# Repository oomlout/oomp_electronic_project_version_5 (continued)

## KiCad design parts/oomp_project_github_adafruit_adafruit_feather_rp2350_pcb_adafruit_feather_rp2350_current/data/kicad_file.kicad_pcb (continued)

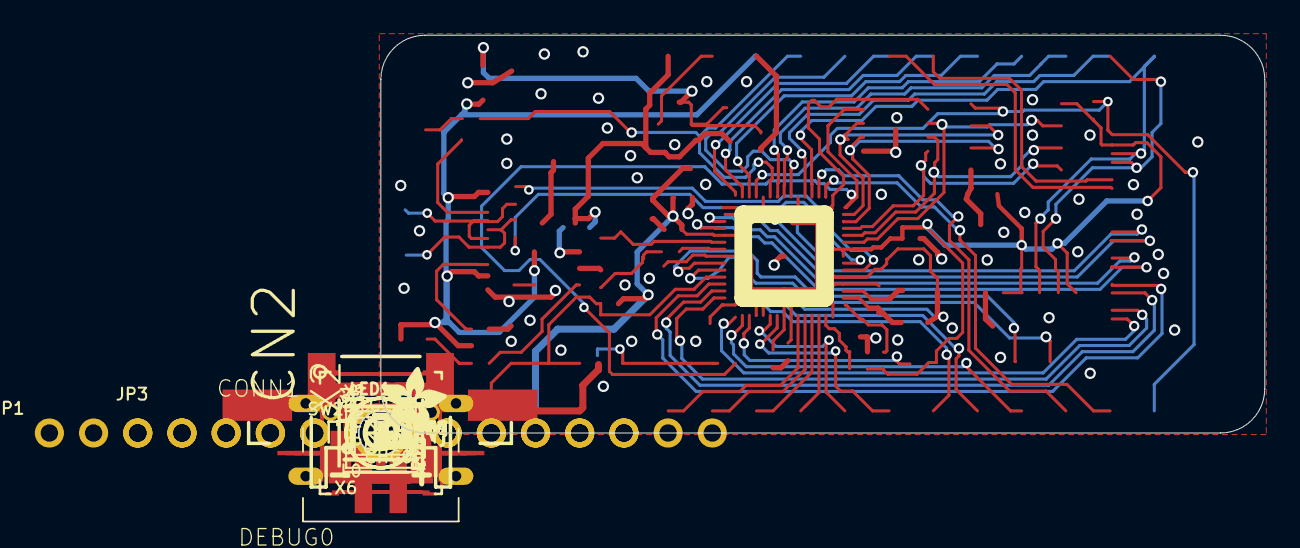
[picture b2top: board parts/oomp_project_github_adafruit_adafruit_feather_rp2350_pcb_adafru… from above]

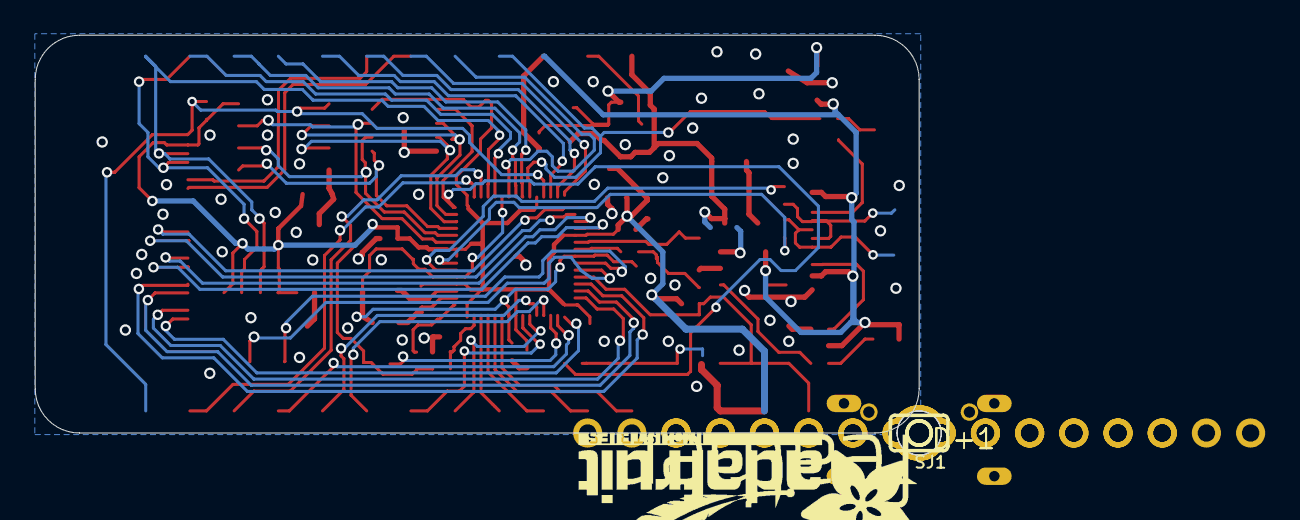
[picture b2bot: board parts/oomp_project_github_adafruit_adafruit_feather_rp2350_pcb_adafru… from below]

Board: 2 copper layers, 50.8 x 22.9 mm, 145 parts (39 on the bottom side), 64 nets.

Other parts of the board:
PLABEL0: PLABEL0
PLABEL1: PLABEL1
PLABEL2: PLABEL2
PLABEL3: PLABEL3
PLABEL4: PLABEL4
PLABEL5: PLABEL5
PLABEL6: PLABEL6
PLABEL7: PLABEL7
PLABEL8: PLABEL8
PLABEL9: PLABEL9
PLABEL10: PLABEL10
PLABEL11: PLABEL11
PLABEL12: PLABEL12
PLABEL13: PLABEL13
PLABEL14: PLABEL14
PLABEL15: PLABEL15
PLABEL16: PLABEL16
PLABEL17: PLABEL17
PLABEL18: PLABEL18
PLABEL19: PLABEL19
PLABEL20: PLABEL20
PLABEL21: PLABEL21
PLABEL22: PLABEL22
PLABEL23: PLABEL23
PLABEL24: PLABEL24
PLABEL25: PLABEL25
PLABEL26: PLABEL26
PLABEL27: PLABEL27
PLABEL28: PLABEL28
PLABEL29: PLABEL29
PLABEL30: PLABEL30
PLABEL31: PLABEL31
PLABEL32: PLABEL32
PLABEL33: PLABEL33
PLABEL34: PLABEL34
PLABEL35: PLABEL35
PLABEL36: PLABEL36
PLABEL37: PLABEL37
PLABEL38: PLABEL38
PLABEL39: PLABEL39
PLABEL40: PLABEL40
PLABEL41: PLABEL41
PLABEL42: PLABEL42
PLABEL43: PLABEL43
PLABEL44: PLABEL44
PLABEL45: PLABEL45
PLABEL46: PLABEL46
PLABEL47: PLABEL47
PLABEL48: PLABEL48
PLABEL49: PLABEL49
PLABEL50: PLABEL50
PLABEL51: PLABEL51
PLABEL52: PLABEL52
PLABEL53: PLABEL53
PLABEL54: PLABEL54
PLABEL55: PLABEL55
PLABEL56: PLABEL56
PLABEL57: PLABEL57
PLABEL58: PLABEL58
PLABEL59: PLABEL59
PLABEL60: PLABEL60
PLABEL61: PLABEL61
PLABEL62: PLABEL62
PLABEL63: PLABEL63
PLABEL64: PLABEL64
PLABEL65: PLABEL65
PLABEL67: PLABEL67
PLABEL68: PLABEL68
U$73: ADAFRUIT_3.5MM
U$74: PCBFEAT-REV-040
U$75: FEATHERLOGO_MED
U$76: ADAFRUIT_TEXT_20MM
UNK_HOLE_0: dummyfp0
UNK_HOLE_1: dummyfp1

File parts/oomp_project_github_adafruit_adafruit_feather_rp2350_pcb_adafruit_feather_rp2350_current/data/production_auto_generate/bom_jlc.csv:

Comment,Designator,Footprint,LCSC Part #
,JP3,Adafruit Feather RP2350-import-fps:1X12_ROUND,C7501588
,JP1,Adafruit Feather RP2350-import-fps:1X16_ROUND,C7501270
,U$73,Adafruit Feather RP2350-import-fps:ADAFRUIT_3.5MM,
,U$76,Adafruit Feather RP2350-import-fps:ADAFRUIT_TEXT_20MM,
,U$75,Adafruit Feather RP2350-import-fps:FEATHERLOGO_MED,
,U$74,Adafruit Feather RP2350-import-fps:PCBFEAT-REV-040,
,PLABEL0,Adafruit Feather RP2350-import-fps:PLABEL0,
,PLABEL1,Adafruit Feather RP2350-import-fps:PLABEL1,
,PLABEL10,Adafruit Feather RP2350-import-fps:PLABEL10,
,PLABEL11,Adafruit Feather RP2350-import-fps:PLABEL11,
,PLABEL12,Adafruit Feather RP2350-import-fps:PLABEL12,
,PLABEL13,Adafruit Feather RP2350-import-fps:PLABEL13,
,PLABEL14,Adafruit Feather RP2350-import-fps:PLABEL14,
,PLABEL15,Adafruit Feather RP2350-import-fps:PLABEL15,
,PLABEL16,Adafruit Feather RP2350-import-fps:PLABEL16,
,PLABEL17,Adafruit Feather RP2350-import-fps:PLABEL17,
,PLABEL18,Adafruit Feather RP2350-import-fps:PLABEL18,
,PLABEL19,Adafruit Feather RP2350-import-fps:PLABEL19,
,PLABEL2,Adafruit Feather RP2350-import-fps:PLABEL2,
,PLABEL20,Adafruit Feather RP2350-import-fps:PLABEL20,
,PLABEL21,Adafruit Feather RP2350-import-fps:PLABEL21,
,PLABEL22,Adafruit Feather RP2350-import-fps:PLABEL22,
,PLABEL23,Adafruit Feather RP2350-import-fps:PLABEL23,
,PLABEL24,Adafruit Feather RP2350-import-fps:PLABEL24,
,PLABEL25,Adafruit Feather RP2350-import-fps:PLABEL25,
,PLABEL26,Adafruit Feather RP2350-import-fps:PLABEL26,
,PLABEL27,Adafruit Feather RP2350-import-fps:PLABEL27,
,PLABEL28,Adafruit Feather RP2350-import-fps:PLABEL28,
,PLABEL29,Adafruit Feather RP2350-import-fps:PLABEL29,
,PLABEL3,Adafruit Feather RP2350-import-fps:PLABEL3,
,PLABEL30,Adafruit Feather RP2350-import-fps:PLABEL30,
,PLABEL31,Adafruit Feather RP2350-import-fps:PLABEL31,
,PLABEL32,Adafruit Feather RP2350-import-fps:PLABEL32,
,PLABEL33,Adafruit Feather RP2350-import-fps:PLABEL33,
,PLABEL34,Adafruit Feather RP2350-import-fps:PLABEL34,
,PLABEL35,Adafruit Feather RP2350-import-fps:PLABEL35,
,PLABEL36,Adafruit Feather RP2350-import-fps:PLABEL36,
,PLABEL37,Adafruit Feather RP2350-import-fps:PLABEL37,
,PLABEL38,Adafruit Feather RP2350-import-fps:PLABEL38,
,PLABEL39,Adafruit Feather RP2350-import-fps:PLABEL39,
,PLABEL4,Adafruit Feather RP2350-import-fps:PLABEL4,
,PLABEL40,Adafruit Feather RP2350-import-fps:PLABEL40,
,PLABEL41,Adafruit Feather RP2350-import-fps:PLABEL41,
,PLABEL42,Adafruit Feather RP2350-import-fps:PLABEL42,
,PLABEL43,Adafruit Feather RP2350-import-fps:PLABEL43,
,PLABEL44,Adafruit Feather RP2350-import-fps:PLABEL44,
,PLABEL45,Adafruit Feather RP2350-import-fps:PLABEL45,
,PLABEL46,Adafruit Feather RP2350-import-fps:PLABEL46,
,PLABEL47,Adafruit Feather RP2350-import-fps:PLABEL47,
,PLABEL48,Adafruit Feather RP2350-import-fps:PLABEL48,
,PLABEL49,Adafruit Feather RP2350-import-fps:PLABEL49,
,PLABEL5,Adafruit Feather RP2350-import-fps:PLABEL5,
,PLABEL50,Adafruit Feather RP2350-import-fps:PLABEL50,
,PLABEL51,Adafruit Feather RP2350-import-fps:PLABEL51,
,PLABEL52,Adafruit Feather RP2350-import-fps:PLABEL52,
,PLABEL53,Adafruit Feather RP2350-import-fps:PLABEL53,
,PLABEL54,Adafruit Feather RP2350-import-fps:PLABEL54,
,PLABEL55,Adafruit Feather RP2350-import-fps:PLABEL55,
,PLABEL56,Adafruit Feather RP2350-import-fps:PLABEL56,
,PLABEL57,Adafruit Feather RP2350-import-fps:PLABEL57,
,PLABEL58,Adafruit Feather RP2350-import-fps:PLABEL58,
,PLABEL59,Adafruit Feather RP2350-import-fps:PLABEL59,
,PLABEL6,Adafruit Feather RP2350-import-fps:PLABEL6,
,PLABEL60,Adafruit Feather RP2350-import-fps:PLABEL60,
,PLABEL61,Adafruit Feather RP2350-import-fps:PLABEL61,
,PLABEL62,Adafruit Feather RP2350-import-fps:PLABEL62,
,PLABEL63,Adafruit Feather RP2350-import-fps:PLABEL63,
,PLABEL64,Adafruit Feather RP2350-import-fps:PLABEL64,
,PLABEL65,Adafruit Feather RP2350-import-fps:PLABEL65,
,PLABEL67,Adafruit Feather RP2350-import-fps:PLABEL67,
,PLABEL68,Adafruit Feather RP2350-import-fps:PLABEL68,
,PLABEL7,Adafruit Feather RP2350-import-fps:PLABEL7,
,PLABEL8,Adafruit Feather RP2350-import-fps:PLABEL8,
,PLABEL9,Adafruit Feather RP2350-import-fps:PLABEL9,
,TP3,Adafruit Feather RP2350-import-fps:TESTPOINT_ROUND_1.5MM_NO,
,"SWC0,SWD0",Adafruit Feather RP2350-import-fps:TESTPOINT_ROUND_1MM,
0.1uF,"C6,C7,C9,C12,C14,C16,C18,C22",Adafruit Feather RP2350-import-fps:_0402NO,C60474
10,R14,Adafruit Feather RP2350-import-fps:_0402NO,C138066
10K,"R2,R3,R4,R5,R7,R15,R16,R17,R21",Adafruit Feather RP2350-import-fps:_0402NO,C2906861
10uF,C5,Adafruit Feather RP2350-import-fps:0603-NO,C19702
10uF,"C1,C4,C20",Adafruit Feather RP2350-import-fps:0805-NO,
10uF_0603,"C8,C13",Adafruit Feather RP2350-import-fps:_0603MP,C19702
12MHz/10pF/50ohm,Y1,Adafruit Feather RP2350-import-fps:CRYSTAL_2.5X2,
15pF,"C2,C3",Adafruit Feather RP2350-import-fps:_0402NO,C106997
1K,"R6,R11",Adafruit Feather RP2350-import-fps:_0402NO,C2906864
1uF,"C10,C11,C15,C17",Adafruit Feather RP2350-import-fps:_0402NO,C2887021
2.2uF,"C19,C21",Adafruit Feather RP2350-import-fps:_0402NO,C12530
200,R1,Adafruit Feather RP2350-import-fps:_0402NO,C25087
22p TOPCONTACT 0.5mm FPC,CN2,Adafruit Feather RP2350-import-fps:FPC_22PIN,
27 ohm,"R9,R10",Adafruit Feather RP2350-import-fps:_0402NO,C25100
5.1K,"R8,R12,R13",Adafruit Feather RP2350-import-fps:_0402NO,C25905
8MB QSPI,U1,Adafruit Feather RP2350-import-fps:USON8_4X4,
DFE252012F-3R3M=P2,L1,Adafruit Feather RP2350-import-fps:INDUCTOR_1007,
DMG3415UFY,Q3,Adafruit Feather RP2350-import-fps:DFN2015-3,
DNP,X2,Adafruit Feather RP2350-import-fps:QFN60_7MM_REDUCEDEPAD,
DNP,U4,Adafruit Feather RP2350-import-fps:SOIC8_150MIL,
FIDUCIAL_1MM,"U$34,U$35",Adafruit Feather RP2350-import-fps:FIDUCIAL_1MM,
JST_SH3,DEBUG0,Adafruit Feather RP2350-import-fps:JST_SH3_RA,
JSTPH,X1,Adafruit Feather RP2350-import-fps:JSTPH2_BATT,
KMR2,"SW1,SW2",Adafruit Feather RP2350-import-fps:BTN_RKB2_4.6X2.8,
MCP73831T-2ACI/OT,U3,Adafruit Feather RP2350-import-fps:SOT23-5,
ORANGE,CHG0,Adafruit Feather RP2350-import-fps:CHIPLED_0603_NOOUTLINE,
PMEG2020AEA,D4,Adafruit Feather RP2350-import-fps:SOD-323F,
RED,L0,Adafruit Feather RP2350-import-fps:CHIPLED_0603_NOOUTLINE,
RT9080-3.3,U2,Adafruit Feather RP2350-import-fps:SOT23-5,
STEMMA_I2C_QTRA,CONN1,Adafruit Feather RP2350-import-fps:JST_SH4_RA,
"TPB1,27","D+1,D-1","Adafruit Feather RP2350-import-fps:B1,27",
USB Type C,X6,Adafruit Feather RP2350-import-fps:USB_C_CUSB31-CFM2AX-01-X,
WS2812B_SK6805_1515,LED1,Adafruit Feather RP2350-import-fps:SK6805_1515,

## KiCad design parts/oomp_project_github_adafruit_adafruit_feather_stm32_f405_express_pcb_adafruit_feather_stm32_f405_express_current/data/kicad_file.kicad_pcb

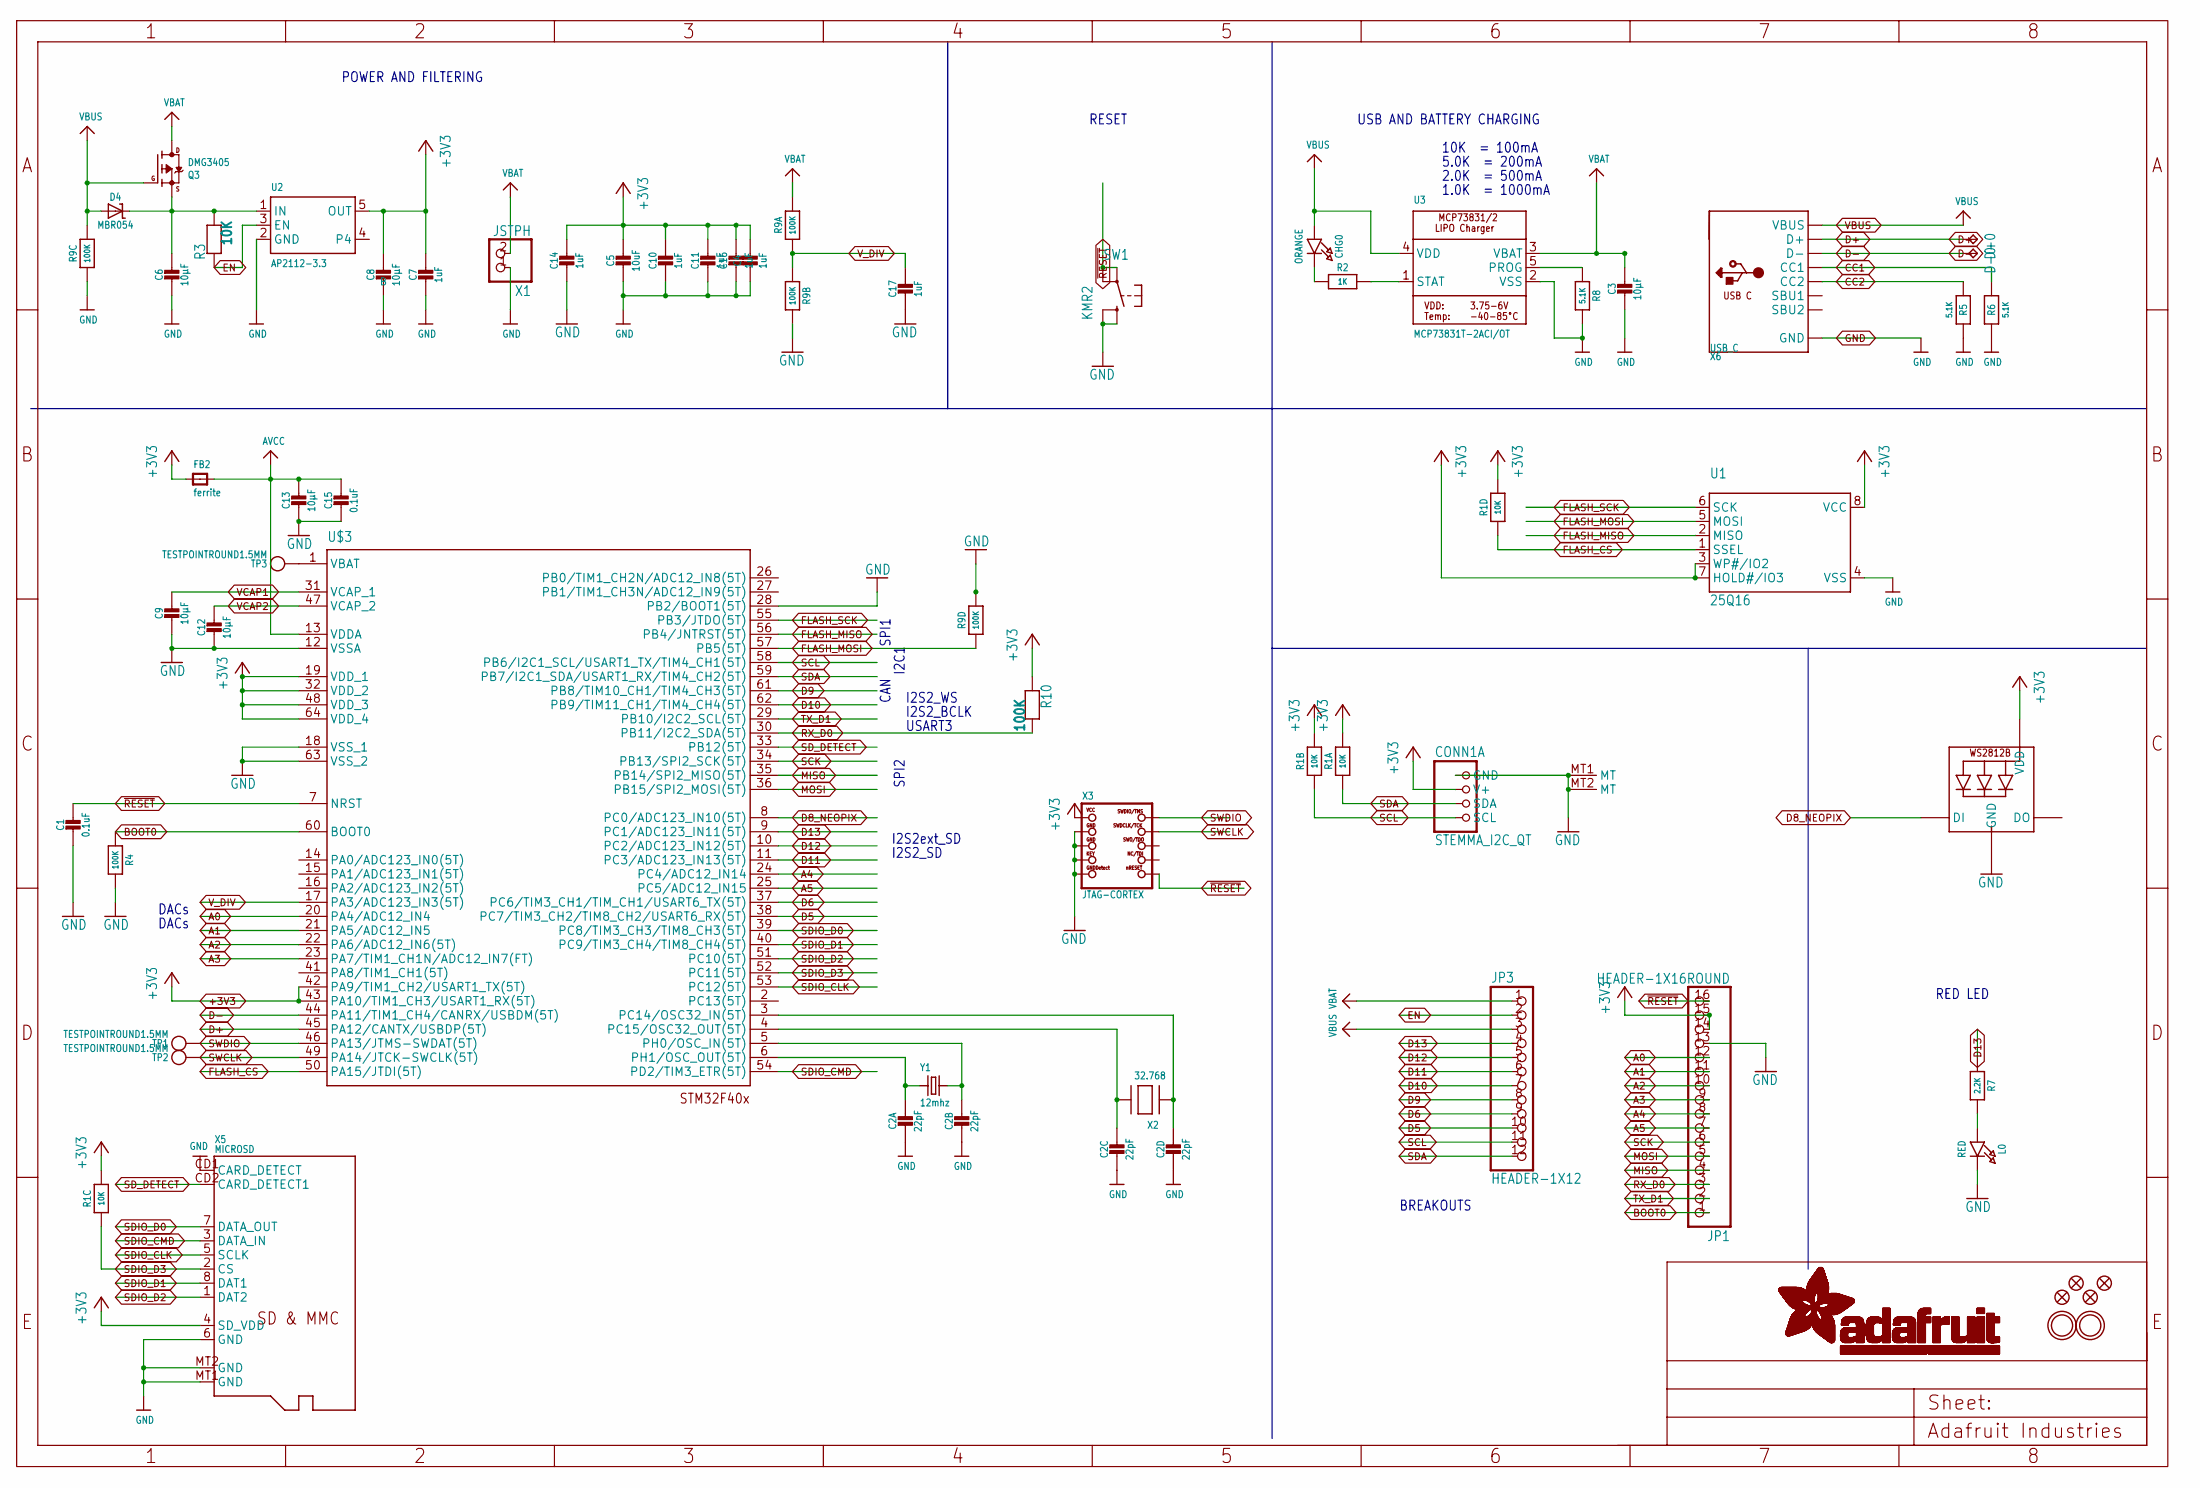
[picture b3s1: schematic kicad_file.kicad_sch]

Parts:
C1, C15: 0.1uF; 0603-NO
C2: 22pF; RESPACK_4X0603
C3, C6, C8, C9, C12, C13: 10µF; 0805-NO
C4, C7, C10, C11, C14, C16, C17: 1uF; 0603-NO
C5: 10uF; 0805-NO
CHG0: ORANGE; CHIPLED_0805_NOOUTLINE
CONN1: STEMMA_I2C_QT; JST_SH4
D4: MBR054; SOD-123
D+0: TPB1,27; B1,27
D-0: TPB1,27; B1,27
FB2: ferrite; 0805-NO
JP1: HEADER-1X16ROUND; 1X16_ROUND
JP3: HEADER-1X12; 1X12_ROUND
L0: RED; CHIPLED_0805_NOOUTLINE
LED1: WS2812B3535; LED3535
Q3: DMG3405; SOT23-R
R1: 10K; RESPACK_4X0603_NO
R2: 1K; 0603-NO
R3: 10K; 0603-NO
R4, R10: 100K; 0603-NO
R5, R6, R8: 5.1K; 0603-NO
R7: 2.2K; 0603-NO
R9: 100K; RESPACK_4X0603_NO
SW1: KMR2; BTN_KMR2_4.6X2.8
TP1, TP2, TP3: TESTPOINTROUND1.5MM; TESTPOINT_ROUND_1.5MM
U1: 25Q16; SOIC8_150MIL
U2: AP2112-3.3; SOT23-5
U3: MCP73831T-2ACI/OT; SOT23-5
U$3: STM32F405R; TQFP64
U$5, U$34, U$35, U$37: FIDUCIAL_1MM
U$31, U$32: MOUNTINGHOLE2.5; MOUNTINGHOLE_2.5_PLATED
X1: JSTPH; JSTPH2
X2: 32.768; XTAL3215
X3: JTAG-CORTEX; 2X05_1.27MM_SMT
X5: MICROSD
X6: USB_C; USB_C_CUSB31-CFM2AX-01-X
Y1: 12mhz; CRYSTAL_2.5X2

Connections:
+3V3: C4.1, C5.1, C7.1, C8.1, C10.1, C11.1, C14.1, C16.1, CONN1.2 (V+), FB2.1, JP1.14, JP1.15, LED1.2 (VDD), R1.5 (2), R1.6 (2), R1.7 (2), R1.8 (2), R10.1, U1.3 (WP#/IO2), U1.7 (HOLD#/IO3), U1.8 (VCC), U2.5 (OUT), U$3.19 (VDD_1), U$3.32 (VDD_2), U$3.42 (PA9/TIM1_CH2/USART1_TX(5T)), U$3.43 (PA10/TIM1_CH3/USART1_RX(5T)), U$3.48 (VDD_3), U$3.64 (VDD_4), X3.1 (VCC), X5.4 (SD_VDD)
A0: JP1.12, U$3.20 (PA4/ADC12_IN4)
A1: JP1.11, U$3.21 (PA5/ADC12_IN5)
A2: JP1.10, U$3.22 (PA6/ADC12_IN6(5T))
A3: JP1.9, U$3.23 (PA7/TIM1_CH1N/ADC12_IN7(FT))
A4: JP1.8, U$3.24 (PC4/ADC12_IN14)
A5: JP1.7, U$3.25 (PC5/ADC12_IN15)
AVCC: C13.1, C15.1, FB2.2, U$3.13 (VDDA)
BATTERY: TP3.P$1, U$3.1 (VBAT)
BOOT0: JP1.1, R4.1, U$3.60 (BOOT0)
CC1: R6.2, X6.A5 (CC1)
CC2: R5.2, X6.B5 (CC2)
D5: JP3.10, U$3.38 (PC7/TIM3_CH2/TIM8_CH2/USART6_RX(5T))
D6: JP3.9, U$3.37 (PC6/TIM3_CH1/TIM_CH1/USART6_TX(5T))
D8_NEOPIX: LED1.1 (DI), U$3.8 (PC0/ADC123_IN10(5T))
D9: JP3.8, U$3.61 (PB8/TIM10_CH1/TIM4_CH3(5T))
D10: JP3.7, U$3.62 (PB9/TIM11_CH1/TIM4_CH4(5T))
D11: JP3.6, U$3.11 (PC3/ADC123_IN13(5T))
D12: JP3.5, U$3.10 (PC2/ADC123_IN12(5T))
D13: JP3.4, R7.1, U$3.9 (PC1/ADC123_IN11(5T))
D+: D+0.TP, U$3.45 (PA12/CANTX/USBDP(5T)), X6.A6 (D+), X6.B6 (D+)
D-: D-0.TP, U$3.44 (PA11/TIM1_CH4/CANRX/USBDM(5T)), X6.A7 (D-), X6.B7 (D-)
EN: JP3.2, R3.1, U2.3 (EN)
FLASH_CS: R1.4 (1), U1.1 (SSEL), U$3.50 (PA15/JTDI(5T))
FLASH_MISO: U1.2 (MISO), U$3.56 (PB4/JNTRST(5T))
FLASH_MOSI: R9.4 (1), U1.5 (MOSI), U$3.57 (PB5(5T))
FLASH_SCK: U1.6 (SCK), U$3.55 (PB3/JTDO(5T))
GND: C1.2, C2.5 (2), C2.6 (2), C2.7 (2), C2.8 (2), C3.2, C4.2, C5.2, C6.2, C7.2, C8.2, C9.2, C10.2, C11.2, C12.2, C13.2, C14.2, C15.2, C16.2, C17.2, CONN1.1 (GND), CONN1.MT1 (MT), CONN1.MT2 (MT), JP1.13, L0.C, LED1.4 (GND), R4.2, R5.1, R6.1, R8.2, R9.3 (1), R9.5 (2), R9.7 (2), SW1.B (S), SW1.B' (S1), U1.4 (VSS), U2.2 (GND), U3.2 (VSS), U$3.12 (VSSA), U$3.18 (VSS_1), U$3.28 (PB2/BOOT1(5T)), U$3.63 (VSS_2), X1.1, X3.3 (GND), X3.5 (GND), X3.7 (KEY), X3.9 (GNDDETECT), X5.6 (GND), X5.CD1 (CARD_DETECT), X5.MT1 (GND), X5.MT2 (GND), X6.A1B12 (GND), X6.B1A12 (GND)
MISO: JP1.4, U$3.35 (PB14/SPI2_MISO(5T))
MOSI: JP1.5, U$3.36 (PB15/SPI2_MOSI(5T))
unnamed: CHG0.C, R2.1
unnamed: L0.A, R7.2
unnamed: R2.2, U3.1 (STAT)
unnamed: R8.1, U3.5 (PROG)
unnamed: C2.4 (1), U$3.3 (PC14/OSC32_IN(5T)), X2.P$1
unnamed: C2.2 (1), U$3.5 (PH0/OSC_IN(5T)), Y1.3 (2)
unnamed: C2.3 (1), U$3.4 (PC15/OSC32_OUT(5T)), X2.P$2
unnamed: C2.1, U$3.6 (PH1/OSC_OUT(5T)), Y1.1
RX_D0: JP1.3, R10.2, U$3.30 (PB11/I2C2_SDA(5T))
SCK: JP1.6, U$3.34 (PB13/SPI2_SCK(5T))
SCL: CONN1.4 (SCL), JP3.11, R1.2 (1), U$3.58 (PB6/I2C1_SCL/USART1_TX/TIM4_CH1(5T))
SDA: CONN1.3 (SDA), JP3.12, R1.1, U$3.59 (PB7/I2C1_SDA/USART1_RX/TIM4_CH2(5T))
SDIO_CLK: U$3.53 (PC12(5T)), X5.5 (SCLK)
SDIO_CMD: U$3.54 (PD2/TIM3_ETR(5T)), X5.3 (DATA_IN)
SDIO_D0: U$3.39 (PC8/TIM3_CH3/TIM8_CH3(5T)), X5.7 (DATA_OUT)
SDIO_D1: U$3.40 (PC9/TIM3_CH4/TIM8_CH4(5T)), X5.8 (DAT1)
SDIO_D2: U$3.51 (PC10(5T)), X5.1 (DAT2)
SDIO_D3: R1.3 (1), U$3.52 (PC11(5T)), X5.2 (CS)
SD_DETECT: U$3.33 (PB12(5T)), X5.CD2 (CARD_DETECT1)
SWCLK: TP2.P$1, U$3.49 (PA14/JTCK-SWCLK(5T)), X3.4 (SWDCLK)
SWDIO: TP1.P$1, U$3.46 (PA13/JTMS-SWDAT(5T)), X3.2 (SWDIO)
TX_D1: JP1.2, U$3.29 (PB10/I2C2_SCL(5T))
VBAT: C3.1, JP3.1, Q3.3 (D), R9.8 (2), U3.3 (VBAT), X1.2
VBUS: CHG0.A, D4.A, JP3.3, Q3.1 (G), R9.6 (2), U3.4 (VDD), X6.A4B9 (VBUS), X6.B4A9 (VBUS)
VCAP1: C9.1, U$3.31 (VCAP_1)
VCAP2: C12.1, U$3.47 (VCAP_2)
VHI: C6.1, D4.C, Q3.2 (S), R3.2, U2.1 (IN)
V_DIV: C17.1, R9.1, R9.2 (1), U$3.17 (PA3/ADC123_IN3(5T))
~RESET: C1.1, JP1.16, SW1.A, SW1.A' (P1), U$3.7 (NRST), X3.10 (NRESET)

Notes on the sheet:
USART3
1.0K = 1000mA
5.0K = 200mA
USB AND BATTERY CHARGING
RED LED
I2S2_SD
10K = 100mA
DACs
SPI2
SPI1
I2S2_BCLK
2.0K = 500mA
I2C1
POWER AND FILTERING
I2S2_WS
RESET
I2S2ext_SD
CAN
BREAKOUTS

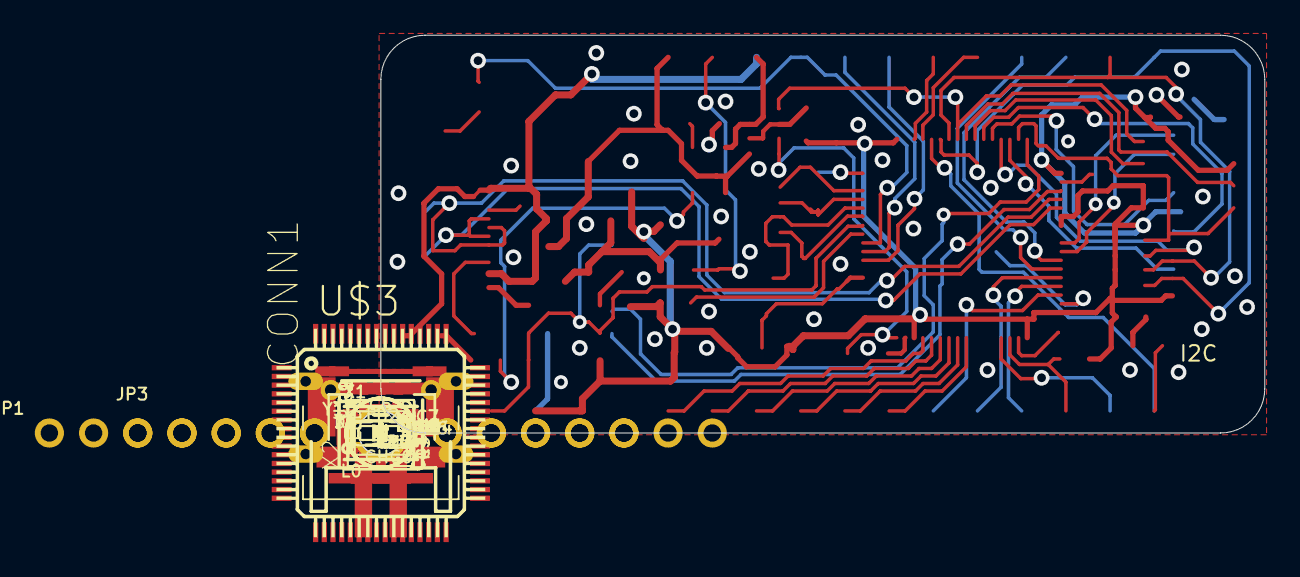
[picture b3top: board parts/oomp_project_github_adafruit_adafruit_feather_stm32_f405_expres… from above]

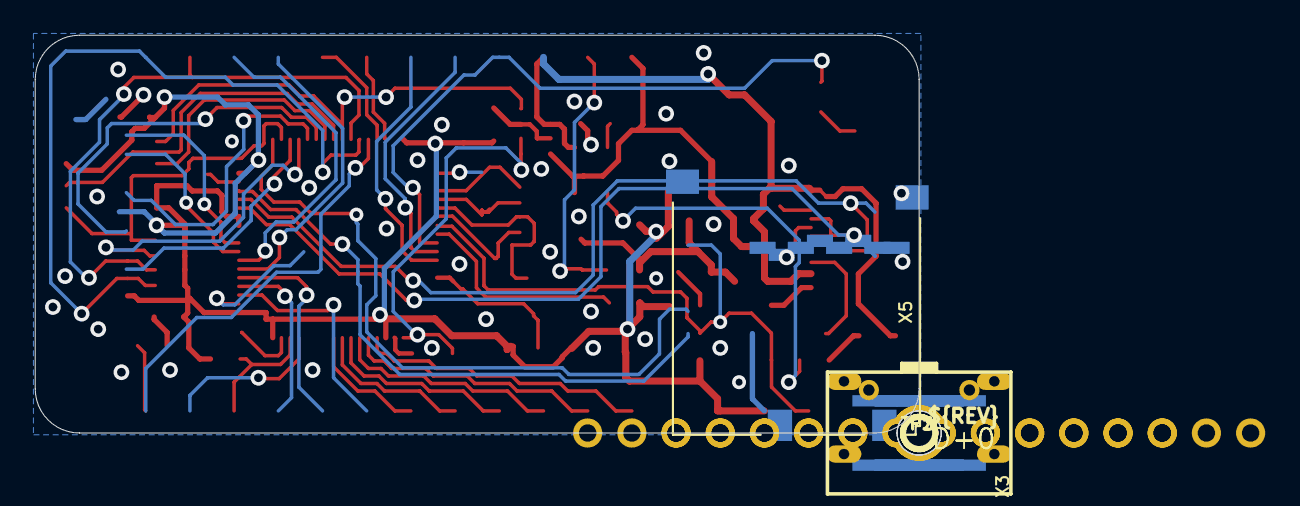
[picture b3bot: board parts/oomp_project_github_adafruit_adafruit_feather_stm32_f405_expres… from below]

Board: 2 copper layers, 50.8 x 22.9 mm, 63 parts (11 on the bottom side), 59 nets.

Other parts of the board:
U$13: PCBFEAT-REV-040
U$24: FEATHER_STM32F405_TOP
U$40: FEATHER_STM32F405_BOT
UNK_HOLE_0: dummyfp0
UNK_HOLE_1: dummyfp1

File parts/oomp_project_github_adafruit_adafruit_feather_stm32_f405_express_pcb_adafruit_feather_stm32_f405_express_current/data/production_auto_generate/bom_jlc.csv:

Comment,Designator,Footprint,LCSC Part #
,JP3,Adafruit Feather STM32F405 Express-import-fps:1X12_ROUND,C7501588
,JP1,Adafruit Feather STM32F405 Express-import-fps:1X16_ROUND,C7501270
,X3,Adafruit Feather STM32F405 Express-import-fps:2X05_1.27MM_SMT,
,U$40,Adafruit Feather STM32F405 Express-import-fps:FEATHER_STM32F405_BOT,
,U$24,Adafruit Feather STM32F405 Express-import-fps:FEATHER_STM32F405_TOP,
,X5,Adafruit Feather STM32F405 Express-import-fps:MICROSD,
,U$13,Adafruit Feather STM32F405 Express-import-fps:PCBFEAT-REV-040,
,"TP1,TP2,TP3",Adafruit Feather STM32F405 Express-import-fps:TESTPOINT_ROUND_1.5MM,
,X6,Adafruit Feather STM32F405 Express-import-fps:USB_C_CUSB31-CFM2AX-01-X,
0.1uF,"C1,C15",Adafruit Feather STM32F405 Express-import-fps:0603-NO,C14663
100K,"R4,R10",Adafruit Feather STM32F405 Express-import-fps:0603-NO,C25803
100K,R9,Adafruit Feather STM32F405 Express-import-fps:RESPACK_4X0603_NO,C25803
10K,R3,Adafruit Feather STM32F405 Express-import-fps:0603-NO,C98220
10K,R1,Adafruit Feather STM32F405 Express-import-fps:RESPACK_4X0603_NO,C98220
10uF,C5,Adafruit Feather STM32F405 Express-import-fps:0805-NO,
10µF,"C3,C6,C8,C9,C12,C13",Adafruit Feather STM32F405 Express-import-fps:0805-NO,
12mhz,Y1,Adafruit Feather STM32F405 Express-import-fps:CRYSTAL_2.5X2,
1K,R2,Adafruit Feather STM32F405 Express-import-fps:0603-NO,C2907002
1uF,"C4,C7,C10,C11,C14,C16,C17",Adafruit Feather STM32F405 Express-import-fps:0603-NO,C5673
2.2K,R7,Adafruit Feather STM32F405 Express-import-fps:0603-NO,C4190
22pF,C2,Adafruit Feather STM32F405 Express-import-fps:RESPACK_4X0603,C105620
25Q16,U1,Adafruit Feather STM32F405 Express-import-fps:SOIC8_150MIL,
32.768,X2,Adafruit Feather STM32F405 Express-import-fps:XTAL3215,
5.1K,"R5,R6,R8",Adafruit Feather STM32F405 Express-import-fps:0603-NO,C23186
AP2112-3.3,U2,Adafruit Feather STM32F405 Express-import-fps:SOT23-5,
DMG3405,Q3,Adafruit Feather STM32F405 Express-import-fps:SOT23-R,
ferrite,FB2,Adafruit Feather STM32F405 Express-import-fps:0805-NO,
FIDUCIAL_1MM,"U$5,U$34,U$35,U$37",Adafruit Feather STM32F405 Express-import-fps:FIDUCIAL_1MM,
JSTPH,X1,Adafruit Feather STM32F405 Express-import-fps:JSTPH2,
KMR2,SW1,Adafruit Feather STM32F405 Express-import-fps:BTN_KMR2_4.6X2.8,
MBR054,D4,Adafruit Feather STM32F405 Express-import-fps:SOD-123,
MCP73831T-2ACI/OT,U3,Adafruit Feather STM32F405 Express-import-fps:SOT23-5,
ORANGE,CHG0,Adafruit Feather STM32F405 Express-import-fps:CHIPLED_0805_NOOUTLINE,
RED,L0,Adafruit Feather STM32F405 Express-import-fps:CHIPLED_0805_NOOUTLINE,
STEMMA_I2C_QT,CONN1,Adafruit Feather STM32F405 Express-import-fps:JST_SH4,C160404
STM32F405R,U$3,Adafruit Feather STM32F405 Express-import-fps:TQFP64,
"TPB1,27","D+0,D-0","Adafruit Feather STM32F405 Express-import-fps:B1,27",
WS2812B3535,LED1,Adafruit Feather STM32F405 Express-import-fps:LED3535,

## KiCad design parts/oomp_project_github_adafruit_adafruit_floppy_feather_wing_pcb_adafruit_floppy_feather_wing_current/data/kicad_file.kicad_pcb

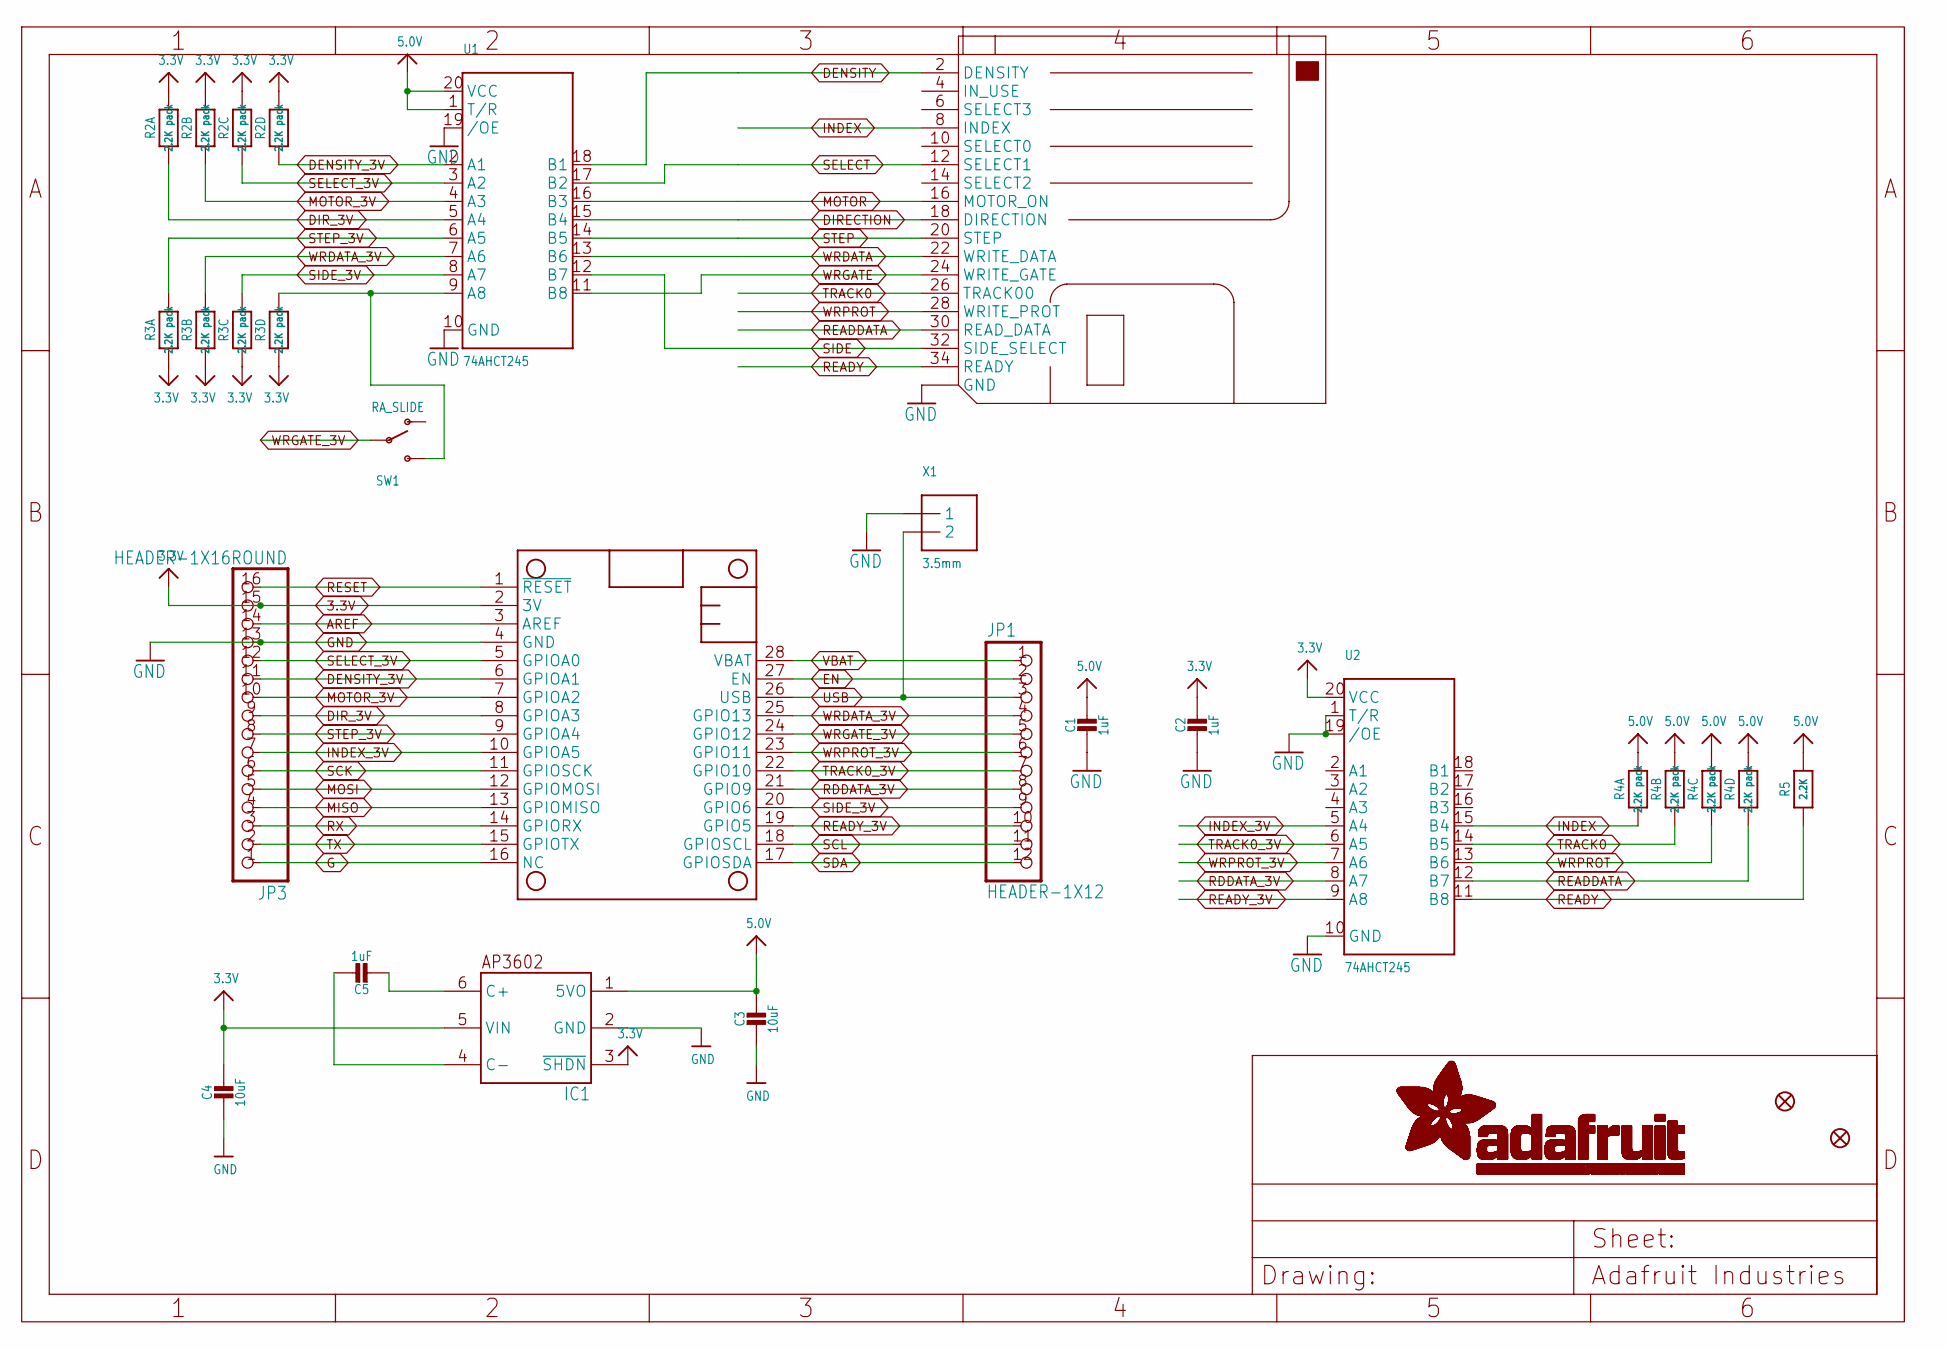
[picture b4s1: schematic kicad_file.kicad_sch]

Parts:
C1, C2, C5: 1uF; 0603-NO
C3, C4: 10uF; 0805-NO
FDD1: FLOPPY_IDC_SMT; 2X17_FLOPPY_SMTIDC
FID1, FID2: FIDUCIAL_1MM
IC1: AP3602; SOT23-6
JP1: HEADER-1X12; 1X12_ROUND
JP3: HEADER-1X16ROUND; 1X16_ROUND
MS1: FEATHERWING
R2, R3, R4: 2.2K pack; RESPACK_4X0603
R5: 2.2K; 0603-NO
SW1: RA_SLIDE; SPDT_SMT_SSSS811101
U1, U2: 74AHCT245; SSOP20
X1: 3.5mm; TERMBLOCK_1X2-3.5MM

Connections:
3.3V: C2.1, C4.1, IC1.3 (~SHDN), IC1.5 (VIN), JP3.15, MS1.2 (3V), R2.5 (2), R2.6 (2), R2.7 (2), R2.8 (2), R3.1, R3.2 (1), R3.3 (1), R3.4 (1), U2.20 (VCC)
5.0V: C1.1, C3.1, IC1.1 (5VO), R4.5 (2), R4.6 (2), R4.7 (2), R4.8 (2), R5.2, U1.1 (T/R), U1.20 (VCC)
AREF: JP3.14, MS1.3 (AREF)
DENSITY: FDD1.2 (DENSITY), U1.18 (B1)
DENSITY_3V: JP3.11, MS1.6 (GPIOA1), R2.4 (1), U1.2 (A1)
DIRECTION: FDD1.18 (DIRECTION), U1.15 (B4)
DIR_3V: JP3.9, MS1.8 (GPIOA3), R2.1, U1.5 (A4)
EN: JP1.2, MS1.27 (EN)
G: JP3.1, MS1.16 (NC)
GND: C1.2, C2.2, C3.2, C4.2, FDD1.1 (GND), FDD1.3 (GND), FDD1.5 (GND), FDD1.7 (GND), FDD1.9 (GND), FDD1.11 (GND), FDD1.13 (GND), FDD1.15 (GND), FDD1.17 (GND), FDD1.19 (GND), FDD1.21 (GND), FDD1.23 (GND), FDD1.25 (GND), FDD1.27 (GND), FDD1.29 (GND), FDD1.31 (GND), FDD1.33 (GND), IC1.2 (GND), JP3.13, MS1.4 (GND), U1.10 (GND), U1.19 (/OE), U2.1 (T/R), U2.10 (GND), U2.19 (/OE), X1.1
INDEX: FDD1.8 (INDEX), R4.1, U2.15 (B4)
INDEX_3V: JP3.7, MS1.10 (GPIOA5), U2.5 (A4)
MISO: JP3.4, MS1.13 (GPIOMISO)
MOSI: JP3.5, MS1.12 (GPIOMOSI)
MOTOR: FDD1.16 (MOTOR_ON), U1.16 (B3)
MOTOR_3V: JP3.10, MS1.7 (GPIOA2), R2.2 (1), U1.4 (A3)
unnamed: R3.5 (2), SW1.C (S), U1.9 (A8)
unnamed: C5.2, IC1.6 (C+)
unnamed: C5.1, IC1.4 (C-)
RDDATA_3V: JP1.8, MS1.21 (GPIO9), U2.8 (A7)
READDATA: FDD1.30 (READ_DATA), R4.4 (1), U2.12 (B7)
READY: FDD1.34 (READY), R5.1, U2.11 (B8)
READY_3V: JP1.10, MS1.19 (GPIO5), U2.9 (A8)
RESET: JP3.16, MS1.1 (~RESET)
RX: JP3.3, MS1.14 (GPIORX)
SCK: JP3.6, MS1.11 (GPIOSCK)
SCL: JP1.11, MS1.18 (GPIOSCL)
SDA: JP1.12, MS1.17 (GPIOSDA)
SELECT: FDD1.12 (SELECT1), U1.17 (B2)
SELECT_3V: JP3.12, MS1.5 (GPIOA0), R2.3 (1), U1.3 (A2)
SIDE: FDD1.32 (SIDE_SELECT), U1.12 (B7)
SIDE_3V: JP1.9, MS1.20 (GPIO6), R3.6 (2), U1.8 (A7)
STEP: FDD1.20 (STEP), U1.14 (B5)
STEP_3V: JP3.8, MS1.9 (GPIOA4), R3.8 (2), U1.6 (A5)
TRACK0: FDD1.26 (TRACK00), R4.2 (1), U2.14 (B5)
TRACK0_3V: JP1.7, MS1.22 (GPIO10), U2.6 (A5)
TX: JP3.2, MS1.15 (GPIOTX)
USB: JP1.3, MS1.26 (USB), X1.2
VBAT: JP1.1, MS1.28 (VBAT)
WRDATA: FDD1.22 (WRITE_DATA), U1.13 (B6)
WRDATA_3V: JP1.4, MS1.25 (GPIO13), R3.7 (2), U1.7 (A6)
WRGATE: FDD1.24 (WRITE_GATE), U1.11 (B8)
WRGATE_3V: JP1.5, MS1.24 (GPIO12), SW1.B
WRPROT: FDD1.28 (WRITE_PROT), R4.3 (1), U2.13 (B6)
WRPROT_3V: JP1.6, MS1.23 (GPIO11), U2.7 (A6)
